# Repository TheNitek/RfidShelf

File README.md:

# RfidShelf
Make your shelf play MP3s!

Use some cheap hardware (Esp8266/NodeMcu, RC522, VS1053 MP3 breakout board) to create an RFID controlled MP3 (and more) shelf. Impression of the first prototype:

This is how the first "test subject" reacted:

## The idea
When I was a little child I loved my tapes, vinyls and later CDs. Choosing my own music or listening to Pumuckl all day. Nowadays everything is available as MP3 which makes it hard for little kids to choose their own music. Since I wanted to give my son the same possibilities I decided to start this project:

Rfid cards can the be assigned a folder containing MP3 files on a SD card, played when the card is put on the shelf. Using some creativity (and/or the Internet and a printer) those cards can be customized to represent their content, giving the kid the ability to distinguish them. A WiFi web interface gives you the ability to manage the files on the shelf and to program the cards.

## Features
* Easy to use: kids proof!
* Safe: No wiring on the outside, just a USB cable going in
* Cheap: ~ 30€ depending on the parts you choose
* Easy to manage: Web interface to configure everything needed

## Repository structure
* /Fritzing contains the sources for the wiring diagram
* /RfidShelf Arduino/platformio sources for building the firmware
* /RfidShelf/build/ current firmware image
* /ShelfBoard KiCad source files for the shelf board pcb
* /ShelfBoard/gerber current shelf board gerber files

## Tools required
* Electric drill
* Hole saw (if you don't have one, you can [get it at ikea](http://www.ikea.com/us/en/catalog/products/20302332/) together with the shelf)
* Soldering iron
* Long, stable screw driver or something similar

## Hardware
I tried a variety of hardware combinations both focusing on being cheap and easy to assemble. Based on that I can recommend a few setups, depending on your budget and your ability/willingness to solder. Most items can be bought on Aliexpress for a few bucks, the links are only meant to be an example.

### Common for all:
Some light soldering is required to attach the pin headers to the MFRC-522

* [Shelf (All Ikea Lack Shelfs and even Tables should work, but I only tried the one linked) ~6€](http://www.ikea.com/de/de/catalog/products/50282177/)
* [NodeMcu (make sure to get correct version, because the vary in size!) ~2,50€](https://www.aliexpress.com/item/V3-Wireless-module-NodeMcu-4M-bytes-Lua-WIFI-Internet-of-Things-development-board-based-ESP8266-for/32554198757.html)
* [MFRC-522 Rfid Reader ~1,50€](https://www.aliexpress.com/item/Free-shipping-MFRC-522-RC522-RFID-RF-IC-card-sensor-module-to-send-S50-Fudan-card/1623810751.html)
* [3W 8Ohm In-Ceiling Speaker ~6,50€](https://www.ebay.de/itm/Decken-Einbaulautsprecher-Mini-Halogen-Look-8cm-6cm-Einbau-weis/222389981849)
* [USB Connector ~1,50€](https://www.aliexpress.com/item/D-type-aluminum-USB-3-0-female-to-female-connector/32608847792.html)
* [Rfid Cards ~0,25€ each](http://www.ebay.de/itm/10pcs-NFC-thin-smart-card-tag-1k-S50-IC-13-56MHz-Read-Write-RFID-/172309355607?hash=item281e701c57)
* Micro USB Cable + USB Power Supply (Just use one from your old smart phone)
* Jumper Wires

### Cheap (~30€)
Disclaimer: I had some noise issues with this version, probably due to all the wires flying around.
Some more light soldering is required to attach the pin headers to the amplifier.
* [Base plate for NodeMcu (also available as a kit including the NodeMcu) ~1,50](https://www.aliexpress.com/item/Nodemcu-base-plate-Lua-WIFI-NodeMcu-development-board-ESP8266-serial-port/32678372845.html)
* [VS1053 MP3 + SD Board ~6,50€](https://www.aliexpress.com/item/VS1053-VS1053B-MP3-Module-Breakout-Board-With-SD-Card-Slot-VS1053B-Ogg-Real-time-Recording-For/32809994212.html)
* [PAM8302 Amplifier ~1,00€](https://www.aliexpress.com/item/CJMCU-832-PAM8302-2-5W-single-channel-Class-D-Audio-power-amplifier-module-PAM8302A-development-board/32708571731.html)
* SD Card (NOT a micro SD but a big one!)

### ShelfBoard based (~40€)
The ShelfBoard comes in 4 pack when ordered at PCBs.io, so if you build more shelves or share with someone else, the price is quite good. Components are the same as for the "cheap" version, but instead of the base plate use the following:
* [ShelfBoard (~10,00€)](https://PCBs.io/share/z7aNg).
* [2.54mm single row female pin header - 15 pin](https://www.aliexpress.com/item/Pitch-2-54mm-2-3-4-5-6-7-8-9-10-11-12-13-14/32793723098.html)
* [2.54mm single row right angle male pin header ](https://www.aliexpress.com/item/10Pcs-40Pin-2-54mm-Single-Row-Right-Angle-Pin-Header-Strip-kit/32664627220.html)
* [2.54 single row right angle female pin header - 10 pin](http://www.ebay.de/itm/Stk-5x-BUCHSENLEISTE-HEADER-10-polig-2-54mm-Abgewinkelt-Right-Angle-A1761-/262828334819?hash=item3d31ca1ee3:g:prkAAOSwImRYjcnX)

### Easy (~45€)
The Adafruit board offers a good sound quality and already has an amp on board. Be sure to by the correct board, there is also a version without the amp, but a phone jack instead!
* [Base plate for NodeMcu (also available as a kit including the NodeMcu) ~1,50](https://www.aliexpress.com/item/Nodemcu-base-plate-Lua-WIFI-NodeMcu-development-board-ESP8266-serial-port/32678372845.html)
* [Adafruit Music Maker FeatherWing w/ Amp ~30,00€](https://www.adafruit.com/product/3436)
* A MicroSD Card

## Wiring

(See /Fritzing folder for vector/svg version if this image)

## Build Instructions
See [hardware instructions](hardware-instructions.md)

## Firmware Flashing
See [firmware flashing](RfidShelf/installation.md)

## Random Notes
* Instead of cards you can also use those blue key fob Rfid tags, like the one included in most MFRC-522 kits. Maybe you can "implant" it into a teddy or something similar.
* Neutrik NAUSB-W seems to be a great alternative for the USB port if manage to get it for a fair price at ebay. It fits a round whole and therefore is easier to mount into the shelf.

## Similar Projects
If the RfidShelf does not fit your needs you might want to have a look here:
* [TonUINO](https://www.voss.earth/tonuino/) (german)

## Disclaimer
Everything in this project I did up to my best knowledge. Nevertheless this comes without guarantee. Do not hold me responsible in case something unexpected/undesired happens.

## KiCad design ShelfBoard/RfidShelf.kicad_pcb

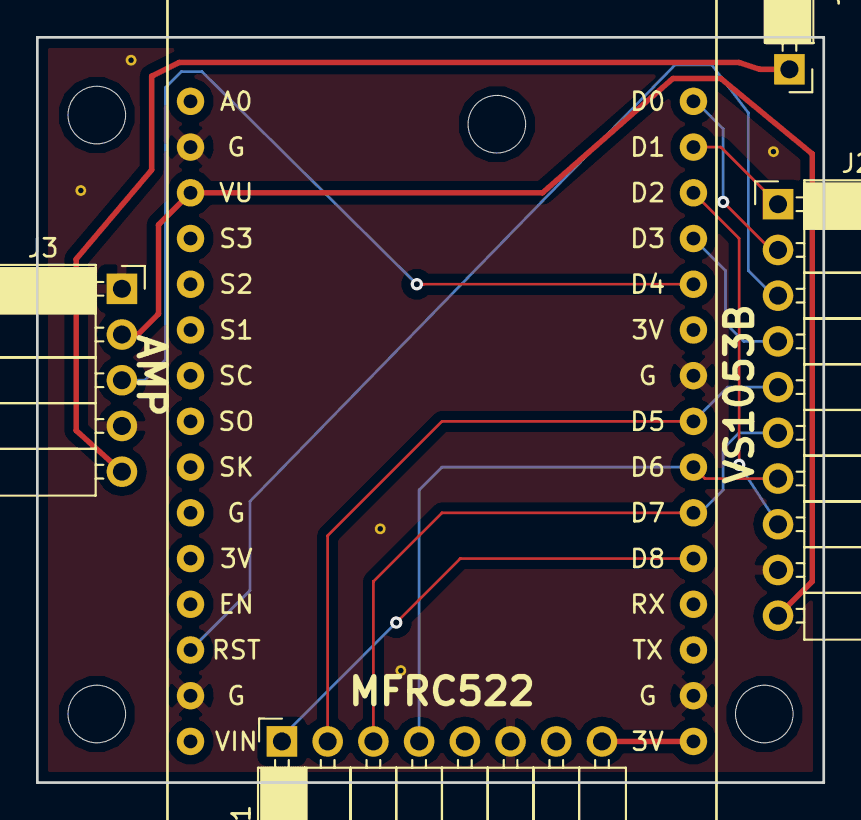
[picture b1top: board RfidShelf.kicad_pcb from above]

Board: 2 copper layers, 43.7 x 41.4 mm, 5 parts (0 on the bottom side), 14 nets.

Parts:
J1: RC522 Header; Socket_Strip_Angled_1x08_Pitch2.54mm
J2: GEEETECH_MP3; Socket_Strip_Angled_1x10_Pitch2.54mm
J3: Amplifier; Socket_Strip_Angled_1x05_Pitch2.54mm
J4: Audio In; Socket_Strip_Angled_1x01_Pitch2.54mm
U1: NodeMCU_1.0_(ESP-12E); NodeMCU1.0(12-E)

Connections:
+3V3: J1.8, U1.16
+5V: J2.10, J3.2, U1.3
/AMP_SLP: J3.3, U1.26
/AUD+: J3.5, J4.1
/DREQ: J2.1, U1.29
/MISO: J1.4, J2.7, U1.22
/MOSI: J1.3, J2.6, U1.21
/RF_CS: J1.1, U1.20
/RST: J2.3, U1.13
/SCLK: J1.2, J2.5, U1.23
/SD_CS: J2.8, U1.28
/XCS: J2.4, U1.27
/XDCS: J2.2, U1.30
GND: J1.6, J2.9, J3.1, J3.4, U1.2, U1.14, U1.17, U1.24

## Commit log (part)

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2017-02-16 Add minimal info to Readme.md
2017-02-16 Added initial version of arduino code
2017-03-19 * make it work * add WiFiManager for wifi config * added webinterface for SD management
2017-04-15 Update README.md
    NodeMcu is the way to go now
2017-06-04 * Added platform.io build* Added travis-ci file* Optimized wiring* Play files in alphabetical order
2017-06-04 Fix .travis.yml - part 2
2017-06-04 Fix .travis.yml - part 3
2017-06-05 Adjust notification settings
2017-06-10 Add 2nd youtube link
2017-06-12 Resized huge images
2017-06-12 Minor formatting tweaks
2017-06-16 Minor changes
    * Reformated wiring diagramm
    * Added list of required tools
2017-08-01 Added one click update
2017-08-01 #3 Timeout Wifi setup after 3 minutes and start our own access point
2017-08-01 Add travis-ci badge and cleanup platformio dependencies
2017-10-30 Added instruction photos
2018-01-06 Add currently playing + play button to web interface. Fixed filter to play only mp3 files
2018-01-15 #7 Stop playback when card is removed. Todo: Playback started via web
2018-01-15 #7 make web triggered playback work again
2018-01-15 Improved tag handling (#8)
    * #7 Stop playback when card is removed. Todo: Playback started via web
    * #7 revert something stupid
    * #7 make web triggered playback work again
2018-03-10 added wiring schematic for adafruit, inkl. fritzing file
2018-03-10 changed colors in wiring schematic, moved wiring schematic to wiring section
2018-03-14 Sort images
2018-03-14 #1 add more instructions
2018-03-15 Add new video
2018-03-15 Fix formating
2018-08-17 Fix underflow in volume control
2018-08-17 #6 store volume per folder on card
2018-08-18 Update binary firmware image
2018-08-29 Allow http playback via web interface
2018-08-31 Fixed file deletion
    Made streaming via web interface working
2018-09-05 fix pio build
2018-09-05 Bump version
2018-11-21 Update README.md
    Typo
2018-12-16 Add firmware instructions
2018-12-16 Update installation.md (#20)
    Fixed link to Adafruit Fork
2018-12-17 Improved WebUI * Added progress bar for file upload * Added client side sorting for sd content * Display file size (to make it easier to spot failed uploads)
2019-01-10 First version that compiles without errors \o/
2019-01-10 Try to fix travis.ci build
2019-01-10 Restructure files (#24)
    * First version that compiles without errors \o/
    * Try to fix travis.ci build
    * Make web interface work again
2019-01-10 Update speaker link to similar speaker
2019-01-12 added mdns service
2019-01-12 added basic bass&treble control fixed deprecation warnings
2019-01-12 Rollback deprecation changes since esp8266 2.5 is still beta. Update build
2019-01-12 only show play file button on mp3 files
2019-01-12 Improved playFile. Added skip button. Bumped version
2019-04-26 playback: fix value clamping in volumeUp() (#28)
2019-05-22 moved configuration to separate central file, added pushover notification service, bumped version
2019-05-22 updates regarding new esp8266 sdk (2.5.2)
2019-05-23 added auto download for vs1053 patches
2019-05-23 move ifdef to correct position
2019-05-27 Some improvements and fixes (#29)
    * moved configuration to separate central file, added pushover notification service, bumped version
    * fix missing timer restart
    * updates regarding new esp8266 sdk (2.5.2)
    * added auto download for vs1053 patches
    * lot of changes
    * move ifdef to correct position
2019-06-30 Don't use volume bar as upload progress indicator. Switch +/- buttons
2019-07-28 Implemented #18 (night mode) and removed HTTP playback since it doesn't work anyway
2019-07-31 Implemented resumable playback (#19)
2019-08-03 Bump version to 1.9
2019-08-06 Fix firmware version
2019-09-19 Fix pause/nightmode bugs
2019-09-19 Bump version number
2019-09-21 Rework web interface (1st step), initial integration of NTP in preparation of #33
2019-09-21 Make Serial output configurable
2019-09-25 Lots of refactoring and hopefully fixing #37
2019-09-25 Fix the bugs the refactoring introduced
2019-09-30 More refactoring
2019-10-01 HTML content is now static (progress to #35)
2019-10-01 More Ajax
2019-10-05 (kind of) fixed #35
2019-10-09 Fix #25
2019-10-09 Bump Version to 1.12
2019-10-12 Resolve #38
2019-10-17 Fixed file upload, fixed file deletion
2019-10-17 First version of # naviation
2019-10-21 try github actions
2019-10-21 Switch to github build status badge
2019-12-14 Fix #40, fix uninitialized array nextFile, pin esp8266 framework version due to incompatible new version
2019-12-18 Formatted HTML & JS and added some CSS styling
2019-12-19 added web browser OTA
2019-12-19 Make MDNS work and add option for ArduinoOTA
2019-12-19 Get rid of visible attribute
2019-12-22 added more styling to files and folders, added option for own url for OTA
2019-12-25 Minor UI fixes
2019-12-26 Accept OTA urls from outside
2019-12-30 config to own struct, write and read new params
2019-12-31 implemented stopOnRemove and repeat
2019-12-31 fixed volume setting
2020-01-01 First draft of random playback mode
2020-01-01 updated build files
2020-01-02 Update main.yml
    Added "Upload artifact" and "Release" step
2020-01-02 Don't use master builds for OTA updates
2020-01-02 comparison of RFID_CONFIG_VERSION is more explicit
2020-01-03 Added card-specific configuration options & dialog (#44)
    * Accept OTA urls from outside
    * added first draft of a card configuration dialog
    * config to own struct, write and read new params
    * implemented stopOnRemove and repeat
    * play some status mp3 files
    * fixed volume setting
2020-01-03 Rename confusing JS functions
2020-01-03 Remove broken startup sounds
2020-01-06 every card option has now 3 states (Yes, No, Keep) (#47)
    * every card option has now 3 states (Yes, No, Keep)
    * fresh SelfHtml.cpp and latest.bin build
2020-01-06 Make file playback conform to datasheet
2020-01-17 Update main.yml
    Drop node dependency
2020-01-17 Updated Github Actions (#45)
    Added "Upload artifact" and "Release" step
2020-01-27 Add debugging output (fix happend in the VS1053b lib)
2020-01-28 Rework RFID config handling. Reset pairing form after pairing
2020-01-29 Stop playback when pairing happens. Don't show firmware update in sub folders. Don't play card if reading config block fails
2020-02-17 First draft of shelf configuration via WebUI
2020-03-01 First experiments with EspAsyncWebserver (not stable)
2020-04-09 Added BoolArray as dependency
2020-04-11 Added BoolArray as dependency (#49)
2020-04-13 Fixed alexa support
2020-05-18 Make ESPAlexa work again
2020-12-19 Upgrade ESPAlexa
2020-12-19 Refresh binaries and update github workflow
2020-12-23 Tweak upload performance (Resolves #21 until someone got a better idea)
2021-01-01 Refactored ShelfConfig to be more managable
2021-04-25 Add information on sd card usage
2021-05-01 First draft for podcast support #50
2021-05-08 Rework char[] handling and project structure
2021-05-08 Fix git workflows
2021-05-12 Finished first release candidate of #50
2021-05-31 Add missing files from last commit
2021-06-04 #50 Add web interface for podcasts
2021-10-09 Drop traviCI and try to fix github actions
2021-10-09 try to fix github actions
2021-10-09 Try to fix github workflow
2022-01-22 Rework config and fix VS1053 patch download
2023-01-27 Fix build with latest 3.1.1 core - Finally adds UTF8 support for file names
2024-04-12 Try to make github workflows build webflash
2024-04-12 Add first html draft
2024-04-13 Add manifest.json
2024-06-04 Bump actions/configure-pages from 4 to 5
    Bumps [actions/configure-pages](https://github.com/actions/configure-pages) from 4 to 5.
    - [Release notes](https://github.com/actions/configure-pages/releases)
    - [Commits](https://github.com/actions/configure-pages/compare/v4...v5)
    ---
    updated-dependencies:
    - dependency-name: actions/configure-pages
2024-06-13 Update installation.md
    Add web flashing link
2025-03-25 Allow manual podcast update request
2025-08-25 Bump actions/upload-pages-artifact from 3 to 4
    Bumps [actions/upload-pages-artifact](https://github.com/actions/upload-pages-artifact) from 3 to 4.
    - [Release notes](https://github.com/actions/upload-pages-artifact/releases)
    - [Commits](https://github.com/actions/upload-pages-artifact/compare/v3...v4)
    ---
    updated-dependencies:
    - dependency-name: actions/upload-pages-artifact
2025-08-25 Bump actions/checkout from 4 to 5
    Bumps [actions/checkout](https://github.com/actions/checkout) from 4 to 5.
    - [Release notes](https://github.com/actions/checkout/releases)
    - [Changelog](https://github.com/actions/checkout/blob/main/CHANGELOG.md)
    - [Commits](https://github.com/actions/checkout/compare/v4...v5)
    ---
    updated-dependencies:
2025-11-24 Bump actions/checkout from 5 to 6
    Bumps [actions/checkout](https://github.com/actions/checkout) from 5 to 6.
    - [Release notes](https://github.com/actions/checkout/releases)
    - [Changelog](https://github.com/actions/checkout/blob/main/CHANGELOG.md)
    - [Commits](https://github.com/actions/checkout/compare/v5...v6)
    ---
    updated-dependencies:
2025-11-24 Bump actions/checkout from 5 to 6 (#59)
    Bumps [actions/checkout](https://github.com/actions/checkout) from 5 to 6.
    - [Release notes](https://github.com/actions/checkout/releases)
    - [Changelog](https://github.com/actions/checkout/blob/main/CHANGELOG.md)
    - [Commits](https://github.com/actions/checkout/compare/v5...v6)
    ---
    updated-dependencies:
2025-12-15 Bump actions/cache from 4 to 5 (#60)
    Bumps [actions/cache](https://github.com/actions/cache) from 4 to 5.
    - [Release notes](https://github.com/actions/cache/releases)
    - [Changelog](https://github.com/actions/cache/blob/main/RELEASES.md)
    - [Commits](https://github.com/actions/cache/compare/v4...v5)
    ---
    updated-dependencies:
2026-03-30 Bump actions/configure-pages from 5 to 6
    Bumps [actions/configure-pages](https://github.com/actions/configure-pages) from 5 to 6.
    - [Release notes](https://github.com/actions/configure-pages/releases)
    - [Commits](https://github.com/actions/configure-pages/compare/v5...v6)
    ---
    updated-dependencies:
    - dependency-name: actions/configure-pages
2026-03-30 Bump actions/configure-pages from 5 to 6 (#61)
    Bumps [actions/configure-pages](https://github.com/actions/configure-pages) from 5 to 6.
    - [Release notes](https://github.com/actions/configure-pages/releases)
    - [Commits](https://github.com/actions/configure-pages/compare/v5...v6)
    ---
    updated-dependencies:
    - dependency-name: actions/configure-pages
2026-03-30 Bump actions/deploy-pages from 4 to 5 (#62)
    Bumps [actions/deploy-pages](https://github.com/actions/deploy-pages) from 4 to 5.
    - [Release notes](https://github.com/actions/deploy-pages/releases)
    - [Commits](https://github.com/actions/deploy-pages/compare/v4...v5)
    ---
    updated-dependencies:
    - dependency-name: actions/deploy-pages
2026-04-20 Bump actions/upload-pages-artifact from 4 to 5 (#63)
    Bumps [actions/upload-pages-artifact](https://github.com/actions/upload-pages-artifact) from 4 to 5.
    - [Release notes](https://github.com/actions/upload-pages-artifact/releases)
    - [Commits](https://github.com/actions/upload-pages-artifact/compare/v4...v5)
    ---
    updated-dependencies:
    - dependency-name: actions/upload-pages-artifact
2026-06-22 Bump actions/checkout from 6 to 7
    Bumps [actions/checkout](https://github.com/actions/checkout) from 6 to 7.
    - [Release notes](https://github.com/actions/checkout/releases)
    - [Changelog](https://github.com/actions/checkout/blob/main/CHANGELOG.md)
    - [Commits](https://github.com/actions/checkout/compare/v6...v7)
    ---
    updated-dependencies:
2026-06-29 Bump actions/cache from 5 to 6
    Bumps [actions/cache](https://github.com/actions/cache) from 5 to 6.
    - [Release notes](https://github.com/actions/cache/releases)
    - [Changelog](https://github.com/actions/cache/blob/main/RELEASES.md)
    - [Commits](https://github.com/actions/cache/compare/v5...v6)
    ---
    updated-dependencies:
